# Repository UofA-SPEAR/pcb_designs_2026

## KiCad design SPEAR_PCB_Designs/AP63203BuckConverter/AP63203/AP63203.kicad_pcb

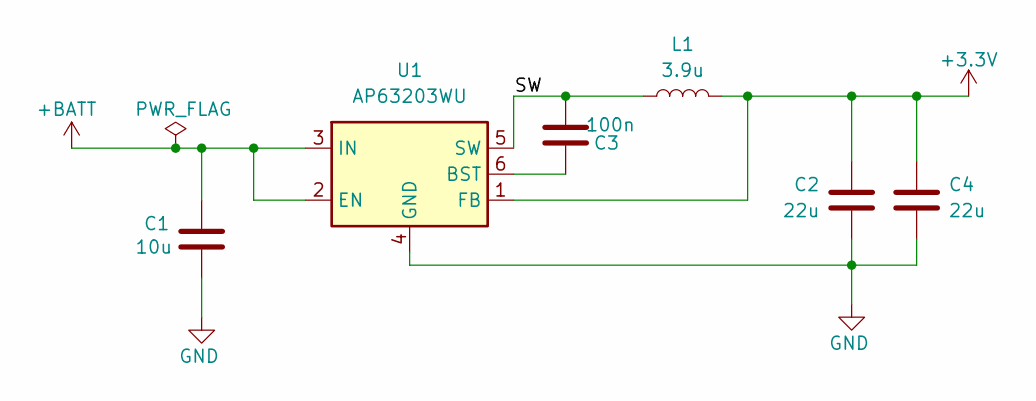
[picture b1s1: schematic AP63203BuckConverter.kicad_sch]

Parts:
C1: 10u; CAP_FG20_TDK_C1
C2, C4: 22u; CAP_FG22_TDK_C2_C4
C3: 100n; C_Disc_D5.0mm_W2.5mm_P5.00mm
L1: 3.9u; L_Wurth_WE-LHMI-1040_L1
U1: AP63203WU; TSOT-23-6

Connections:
+3.3V: C2.1, C4.1, L1.2, U1.1 (FB)
+BATT: C1.1, U1.2 (EN), U1.3 (IN)
/SW: C3.1, L1.1, U1.5 (SW)
GND: C1.2, C2.2, C4.2, U1.4 (GND)
unnamed: C3.2, U1.6 (BST)

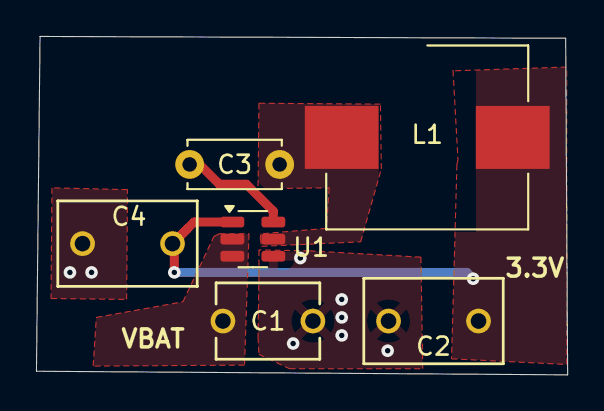
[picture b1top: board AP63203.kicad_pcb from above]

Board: 2 copper layers, 29.5 x 18.8 mm, 6 parts (0 on the bottom side), 5 nets.

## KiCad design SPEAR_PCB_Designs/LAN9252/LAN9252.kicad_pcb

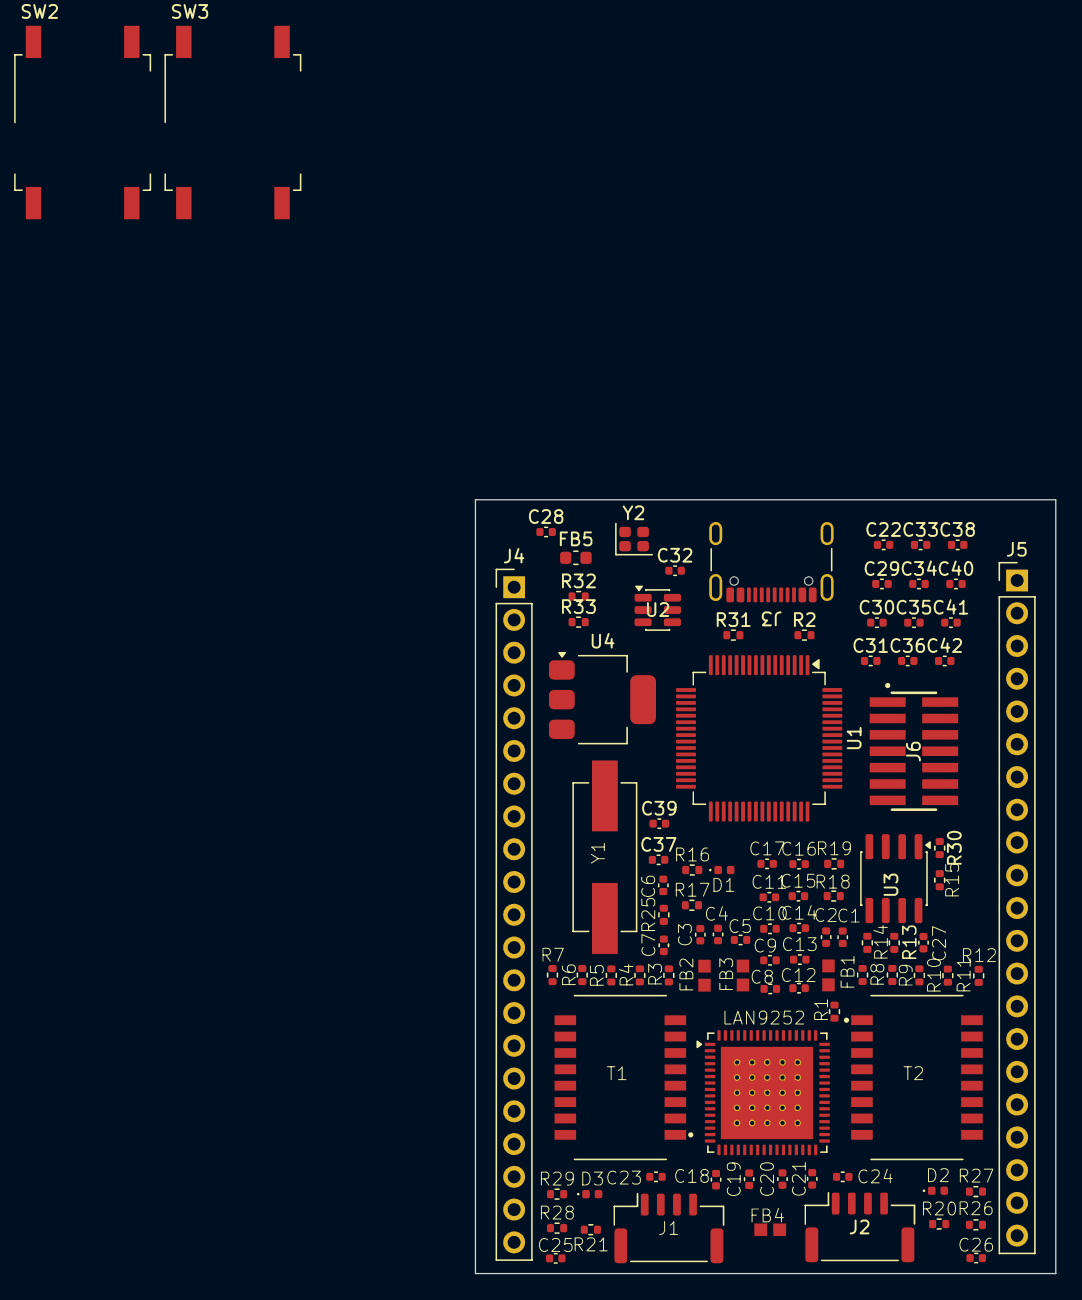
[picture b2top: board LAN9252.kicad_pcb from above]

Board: 4 copper layers, 45.0 x 60.0 mm, 97 parts (0 on the bottom side), 107 nets.

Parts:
C1, C3: 1uF; C_0402_1005Metric
C2, C4, C5, C8, C9, C10, C11, C12, C13, C14, C15, C16, C17, C18, C19, C20, C21: 0.1uF; C_0402_1005Metric
C6, C7: 18pF; C_0402_1005Metric
C22, C29, C31, C32, C34, C35, C38: 100n; C_0402_1005Metric
C23, C24: C; C_0402_1005Metric
C25, C26: 1000 uF; C_0402_1005Metric
C27: 0.1 uF; C_0402_1005Metric
C28, C37: 10u; C_0402_1005Metric
C30, C33: 10p; C_0402_1005Metric
C36: 2.2u; C_0402_1005Metric
C39: 22u; C_0402_1005Metric
C40: 10n; C_0402_1005Metric
C41, C42: 1u; C_0402_1005Metric
D1, D2, D3: LED; LED_0402_1005Metric
FB1, FB2, FB3, FB4: FerrriteBead; Ferrite_bead
FB5: 120R; L_0603_1608Metric
J1, J2: SM04B-GHS-TB; JST_GH_SM04B-GHS-TB_1x04-1MP_P1.25mm_Horizontal
J3: USB_C_Receptacle_USB2.0_16P; USB_C_Receptacle_GCT_USB4105-xx-A_16P_TopMnt_Horizontal
J4, J5: Conn_01x21_Pin; PinHeader_1x21_P2.54mm_Vertical
J6: FTSH-107-01-F-DV-K-P-TR; SAMTEC_FTSH-107-01-F-DV-K-P-TR
LAN9252: LAN9252_QFN UPDATED
R1: 12.1k; R_0402_1005Metric
R2, R31, R32, R33: 5.1k; R_0402_1005Metric
R3, R4, R5, R6, R7, R8, R9, R10, R11, R12: 49.9 R; R_0402_1005Metric
R13, R14: 2kR; R_0402_1005Metric
R15: 4.7kR; R_0402_1005Metric
R16: 270R; R_0402_1005Metric
R17, R18, R19: 10kR; R_0402_1005Metric
R20, R21: 1k; R_0402_1005Metric
R25: 0R; R_0402_1005Metric
R26, R27, R28, R29: 75; R_0402_1005Metric
R30: 100R; R_0402_1005Metric
SW2, SW3: SW_MEC_5E; SW_MEC_5GSH9
T1, T2: H1102NLT; XFMR_H1102NLT
U1: STM32F446RCTx; LQFP-64_10x10mm_P0.5mm
U2: USBLC6-2SC6; SOT-23-6
U3: 24FC512; SOIC-8_3.9x4.9mm_P1.27mm
U4: AMS1117-3.3; SOT-223-3_TabPin2
Y1: 25MHz; Y_Wurth_WE-XTAL_Quartz-HC49-4HSMX
Y2: 16MHz; Crystal_SMD_2016-4Pin_2.0x1.6mm

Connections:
+3.3V: C5.1, C12.1, C13.1, C14.1, C15.1, C16.1, C17.1, C27.1, C28.1, C29.1, C31.1, C34.1, C35.1, C38.1, C39.1, C42.1, D1.2 (A), FB1.1, FB2.1, FB3.2, FB5.2, J4.1, J4.2, J6.03, LAN9252.5 (VDD33), LAN9252.7 (REG_EN), LAN9252.14 (VDDIO), LAN9252.20 (VDDIO__1), LAN9252.32 (VDDIO__2), LAN9252.37 (VDDIO__3), LAN9252.47 (VDDIO__4), R13.1, R14.1, R17.2, SW2.3 (K), SW2.4 (A), U1.1 (VBAT), U1.19 (VDD), U1.32 (VDD), U1.48 (VDD), U1.64 (VDD), U3.8 (VCC), U4.2 (VO)
+3.3VA: C40.1, C41.1, FB5.1, U1.13 (VDDA)
+VBUS: C37.1, J3.A4 (VBUS), J3.A9 (VBUS), J3.B4 (VBUS), J3.B9 (VBUS), U2.5 (VBUS), U4.3 (VI)
/EtherCAT/BOOT0: C32.1, J4.5, R32.1, R33.2, U1.60 (BOOT0)
/EtherCAT/HSE_IN: C30.1, U1.5 (PH0), Y2.1
/EtherCAT/HSE_OUT: C33.1, U1.6 (PH1), Y2.3
/EtherCAT/NRST: C22.1, J4.4, J6.12, SW3.3 (K), SW3.4 (A), U1.7 (NRST)
/EtherCAT/PA0: J4.13, U1.14 (PA0)
/EtherCAT/PA1: J4.14, U1.15 (PA1)
/EtherCAT/PA2/UART2_TX: J6.14, U1.16 (PA2)
/EtherCAT/PA3/UART2_RX: J6.13, U1.17 (PA3)
/EtherCAT/PA4: J4.15, U1.20 (PA4)
/EtherCAT/PA8: J5.9, U1.41 (PA8)
/EtherCAT/PA9: J5.10, U1.42 (PA9)
/EtherCAT/PA10: J5.11, U1.43 (PA10)
/EtherCAT/PA15: J5.12, U1.50 (PA15)
/EtherCAT/PB0: J4.18, U1.26 (PB0)
/EtherCAT/PB1: J4.19, U1.27 (PB1)
/EtherCAT/PB2: J4.20, U1.28 (PB2)
/EtherCAT/PB4: J5.16, U1.56 (PB4)
/EtherCAT/PB5: J5.17, U1.57 (PB5)
/EtherCAT/PB6: J5.18, U1.58 (PB6)
/EtherCAT/PB7: J5.19, U1.59 (PB7)
/EtherCAT/PB8: J5.20, U1.61 (PB8)
/EtherCAT/PB9: J5.21, U1.62 (PB9)
/EtherCAT/PB10: J4.21, U1.29 (PB10)
/EtherCAT/PB12: J5.1, U1.33 (PB12)
/EtherCAT/PB13: J5.2, U1.34 (PB13)
/EtherCAT/PB14: J5.3, U1.35 (PB14)
/EtherCAT/PB15: J5.4, U1.36 (PB15)
/EtherCAT/PC0: J4.9, U1.8 (PC0)
/EtherCAT/PC1: J4.10, U1.9 (PC1)
/EtherCAT/PC2: J4.11, U1.10 (PC2)
/EtherCAT/PC3: J4.12, U1.11 (PC3)
/EtherCAT/PC4: J4.16, U1.24 (PC4)
/EtherCAT/PC5: J4.17, U1.25 (PC5)
/EtherCAT/PC6: J5.5, U1.37 (PC6)
/EtherCAT/PC7: J5.6, U1.38 (PC7)
/EtherCAT/PC8: J5.7, U1.39 (PC8)
/EtherCAT/PC9: J5.8, U1.40 (PC9)
/EtherCAT/PC10: J5.13, U1.51 (PC10)
/EtherCAT/PC11: J5.14, U1.52 (PC11)
/EtherCAT/PC12: J5.15, U1.53 (PC12)
/EtherCAT/PC13: J4.6, U1.2 (PC13)
/EtherCAT/PC14: J4.7, U1.3 (PC14)
/EtherCAT/PC15: J4.8, U1.4 (PC15)
/EtherCAT/SWCLK: J6.06, U1.49 (PA14)
/EtherCAT/SWDIO: J6.04, U1.46 (PA13)
/EtherCAT/SWO: J6.08, U1.55 (PB3)
/EtherCAT/USB_D+: U1.45 (PA12), U2.4 (I/O2)
/EtherCAT/USB_D-: U1.44 (PA11), U2.6 (I/O1)
/GPIO0: LAN9252.48 (LINKACTLED0/TDO/~CHIP_MODE0), R18.2, R21.1
/GPIO1: LAN9252.46 (LINKACTLED1/TDI/~CHIP_MODE1), R19.2, R20.1
/GPIO2: LAN9252.45 (RUNLED/~E2PSIZE), R16.1, R17.1
/I2C_SCL: LAN9252.43 (EESCL/TCK), R13.2, U3.6 (SCL)
/I2C_SDL: LAN9252.42 (EESDA/TMS), R14.2, U3.5 (SDA)
/MISO: LAN9252.13 (D1/SIO1), U1.22 (SPI1_MISO)
/MOSI: LAN9252.17 (D0/SIO0), U1.23 (SPI1_MOSI)
/RXA_N: LAN9252.54 (RXNA), R6.2, T1.8
/RXA_P: LAN9252.55 (RXPA), R5.2, T1.6
/RXB_N: LAN9252.61 (RXNB), R11.2, T2.8
/RXB_P: LAN9252.60 (RXPB), R10.2, T2.6
/SCK: LAN9252.19 (D9/LATCH_IN/SCK), U1.21 (SPI1_SCK)
/TXA_N: LAN9252.52 (TXNA), R4.2, T1.3
/TXA_P: LAN9252.53 (TXPA), R3.2, T1.1
/TXB_N: LAN9252.63 (TXNB), R9.2, T2.3
/TXB_P: LAN9252.62 (TXPB), R8.2, T2.1
/VDD12TX1: C8.1, C9.1, C10.1, C11.1, FB4.1, LAN9252.56 (VDD12TX1), LAN9252.59 (VDD12TX2)
/VDD33TXRX1: C1.1, C2.1, FB1.2, LAN9252.51 (VDD33TXRX1), R3.1, R4.1, R5.1, R6.1, R7.1
/VDD33TXRX2: C3.1, C4.1, FB2.2, LAN9252.64 (VDD33TXRX2), R8.1, R9.1, R10.1, R11.1, R12.1
/VDDCR: C18.1, C19.1, C20.1, C21.1, FB4.2, LAN9252.6 (VDDCR), LAN9252.24 (VDDCR__1), LAN9252.38 (VDDCR__2)
GND: C5.2, C22.2, C28.2, C29.2, C30.2, C31.2, C32.2, C33.2, C34.2, C35.2, C36.2, C37.2, C38.2, C39.2, C40.2, C41.2, C42.2, D2.1 (K), D3.1 (K), J3.A1 (GND), J3.A12 (GND), J3.B1 (GND), J3.B12 (GND), J3.S1 (SHIELD), J4.3, J6.05, J6.07, R2.2, R30.1, R31.2, R32.2, SW3.1, SW3.2, U1.12 (VSSA), U1.18 (VSS), U1.31 (VSS), U1.47 (VSS), U1.63 (VSS), U2.2 (GND), U4.1 (GND), Y2.2, Y2.4
GNDREF: C6.1, C7.1, C8.2, C9.2, C10.2, C11.2, C12.2, C13.2, C14.2, C15.2, C16.2, C17.2, C18.2, C19.2, C20.2, C21.2, C23.2, C24.2, C25.2, C26.2, C27.2, LAN9252.4 (OSCVSS), LAN9252.8 (~FXLOSEN), LAN9252.9 (FXSDA/FXLOSA/~FXSDENA), LAN9252.41 (TESTMODE), LAN9252.65 (VSS), R1.1, R15.1, R18.1, R19.1, U3.4 (VSS)
unnamed: C1.2, C2.2
unnamed: C3.2, C4.2
unnamed: C6.2, R25.1, Y1.2
unnamed: C23.1, R7.2, T1.2, T1.7
unnamed: C24.1, R12.2, T2.2, T2.7
unnamed: C25.1, R28.2, R29.2
unnamed: C26.1, R26.2, R27.2
unnamed: D1.1 (K), R16.2
unnamed: D2.2 (A), R20.2
unnamed: D3.2 (A), R21.2
unnamed: J1.1, T1.16
unnamed: J1.2, T1.14
unnamed: J1.3, T1.11
unnamed: J1.4, T1.9
unnamed: J2.1, T2.16
unnamed: J2.2, T2.14
unnamed: J2.3, T2.11
unnamed: J2.4, T2.9
unnamed: J3.A5 (CC1), R2.1
unnamed: J3.B5 (CC2), R31.1
unnamed: J3.A6 (D+), J3.B6 (D+), U2.3 (I/O2)
unnamed: J3.A7 (D-), J3.B7 (D-), U2.1 (I/O1)
unnamed: J6.11, R30.2
unnamed: LAN9252.1 (OSCI), R25.2
unnamed: C7.2, LAN9252.2 (OSCO), Y1.1
unnamed: LAN9252.57 (RBIAS), R1.2
unnamed: FB3.1, LAN9252.58 (VDD33BIAS)
unnamed: R26.1, T2.15
unnamed: R27.1, T2.10
unnamed: R28.1, T1.15
unnamed: R29.1, T1.10
unnamed: R33.1, SW2.1, SW2.2
unnamed: C36.1, U1.30 (VCAP_1)
unnamed: R15.2, U3.1 (A0), U3.2 (A1), U3.3 (A2), U3.7 (WP)
